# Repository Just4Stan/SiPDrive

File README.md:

# SiPDrive (Work In Progress, Status: Ordering first hardware)

**Compact Field-Oriented Control (FOC) firmware and hardware for QDD actuators**

SiPDrive is an open-source motor controller built around the STSPIN32G4 System-in-Package, MT6701 magnetic encoder, and CAN-FD communication. It targets compact quasi-direct-drive (QDD) actuator applications with torque, position, and speed control.

| | Status |
|---|---|
| **Build** | Compiles (macOS ARM GCC 15.2.0) |
| **Hardware** | PCB designed, ordering assembled from JLCPCB |
| **Firmware** | ~3,100 LOC, 11 KB Flash (8.4%), 13 KB RAM (59%) |
| **License** | CC BY-NC 4.0 |

### Key Features

- 40 kHz FOC current loop with hardware CORDIC acceleration
- CAN-FD command/telemetry (1 Mbps nominal, 5 Mbps data)
- Current and position control modes
- 14-bit magnetic encoder (MT6701 SSI/ABZ selectable via solder jumper)
- On-device encoder calibration with 128-entry compensation table
- Persistent configuration in flash (CRC32 protected)
- Thermal derating and fault protection (board + stator NTC)
- Space Vector PWM (SVPWM) with configurable duty limits

---

## Quick Start

### Prerequisites

```bash
# macOS
brew install arm-none-eabi-gcc cmake
```

### Fetch Dependencies

```bash
cd external
git clone --depth 1 --branch 5.9.0 https://github.com/ARM-software/CMSIS_5.git CMSIS
git clone --depth 1 https://github.com/STMicroelectronics/cmsis_device_g4.git
```

### Build

```bash
cmake -B build \
  -DCMAKE_TOOLCHAIN_FILE=cmake/arm-none-eabi-gcc.cmake \
  -DCMAKE_BUILD_TYPE=Release \
  -DSIPDRIVE_CMSIS_CORE_DIR=external/CMSIS/CMSIS/Core/Include \
  -DSIPDRIVE_STM32G4_DEVICE_DIR=external/cmsis_device_g4

cmake --build build
```

Outputs: `build/SiPDrive.elf`, `.bin`, `.hex`, `.map`

### Flash

```bash
# ST-LINK (recommended)
st-flash write build/SiPDrive.bin 0x08000000

# OpenOCD
openocd -f interface/stlink.cfg -f target/stm32g4x.cfg \
  -c "program build/SiPDrive.elf verify reset exit"
```

---

## Repository Layout

```
SiPDrive/
├── src/                    Firmware source (~3,100 LOC)
├── hw/SiPDrive/            KiCad schematic, PCB, datasheets
├── cmake/                  Toolchain configuration
├── link/                   Linker script (STM32G431)
└── external/               CMSIS dependencies (not vendored)
```

---

<details>
<summary><h2>Hardware Architecture</h2></summary>

### Core Components

**STSPIN32G4 (U1)** - System-in-Package containing:
- STM32G431CBU6 (Cortex-M4F @ 170 MHz)
- Integrated 3-phase gate driver
- Buck converter for MCU power
- 3x operational amplifiers for current sensing
- Memory: 128 KB Flash, 22 KB SRAM + 10 KB CCM RAM

**MT6701 (U2)** - 14-bit magnetic angle sensor
- SSI (default, MODE=HIGH) or ABZ mode (JP1 solder jumper to GND)
- PB7=DO/A, PB6=CLK/B, PB4=CSN/Z

**TCAN1057A (U3)** - CAN-FD transceiver (up to 5 Mbps)

### Pin Assignments

| Peripheral | Function | Pins |
|---|---|---|
| TIM1 | 3-phase PWM (internal to STSPIN32G4 gate driver) | GHS/GLS via 20R gate resistors |
| TIM4 | QEI encoder (ABZ mode) or SPI (SSI mode) | PB7=DO/A, PB6=CLK/B, PB4=CSN/Z |
| OPAMP1 | Phase U current (Ia) | PA1(+), PA3(-), PA2(out) |
| OPAMP2 | Phase W current (Ic) | PA7(+), PC5(-), PA6(out) |
| OPAMP3 | Phase V current (Ib) | PB0(+), PB2(-), PB1(out) |
| ADC1/2 | Vbus, board NTC, stator NTC | PC0 (IN6), PC1 (IN7), PC2 (IN8) |
| FDCAN1 | CAN-FD | PA11=RX, PA12=TX, PA10=TCAN standby |
| I2C3 | STSPIN32G4 gate driver config | Internal SiP bus (no external pins) |
| CORDIC | Hardware sin/cos | - |

### Current Sensing

3-shunt topology with biased differential OPAMPs (EVL reference design):
- **Shunts**: 3x 2 mR (SME08A1FR002T, 0805 1W) on low-side MOSFET sources
- **OPAMP gain**: 10x (Rf=15k / Rin=1.5k), mid-rail bias via 30k/30k divider on OPAMP+ nodes
- **MOSFETs**: 6x CMSA015N06 with 20R gate resistors

### Hardware Constraints

- **128 KB Flash** total - code size must be minimized
- **SCREF overcurrent**: 0.30V threshold via 100k/10k divider (~150A trip with 2 mR shunts)
- **MT6701 MODE**: R6 10k pullup = SSI default, JP1 jumper to GND for ABZ mode
- **Stator NTC (R14)**: DNP solder pad for external thermistor

### KiCad Project

- Schematic: `hw/SiPDrive/SiPDrive.kicad_sch`
- PCB: `hw/SiPDrive/SiPDrive.kicad_pcb`
- Netlist: `hw/SiPDrive/SiPDrive.net`
- Custom libraries: `hw/SiPDrive/kicad/libs/`
- Production outputs: `hw/SiPDrive/production/`

</details>

<details>
<summary><h2>Firmware Architecture</h2></summary>

### Source Layout

| File | Purpose |
|---|---|
| `main.cc` | Main loop, CAN protocol, control loop ISR |
| `config.h` | Compile-time constants |
| `foc_core.{h,cc}` | Clarke/Park transforms, PI current control |
| `position_control.{h,cc}` | Position/velocity PID |
| `calibration.{h,cc}` | Encoder calibration state machine |
| `hal_tim1_pwm.{h,cc}` | TIM1 PWM + 40 kHz ISR |
| `hal_adc_opamp.{h,cc}` | ADC + OPAMP (injected + regular) |
| `hal_qei.{h,cc}` | Quadrature encoder (TIM3/4) |
| `hal_fdcan.{h,cc}` | CAN-FD driver |
| `hal_i2c3_stspin.{h,cc}` | Gate driver I2C config |
| `hal_flash.{h,cc}` | Flash read/write |
| `hal_gpio.{h,cc}` | GPIO utilities |
| `thermal.{h,cc}` | NTC monitoring + derating |
| `persistent_config.{h,cc}` | Flash config (CRC protected) |
| `runtime_support.cc` | Math/string fallbacks (no newlib) |

### Startup Sequence

1. Enable DWT cycle counter
2. Load persistent config from flash (or defaults)
3. Init STSPIN32G4 gate driver via I2C3
4. Init TIM1 PWM (40 kHz) + register ISR
5. Init ADC + OPAMP, calibrate current offsets (1024 samples)
6. Init QEI encoder interface
7. Init FDCAN
8. Apply config (PID gains, thermal limits, calibration)
9. Enable TIM1 and power stage
10. Enter main loop

### Main Loop (~1 kHz)

- Service regular ADC (Vbus, NTC temperatures)
- Update thermal protection
- Handle CAN-FD RX (command frames)
- Run calibration state machine (if active)
- Send telemetry (10 Hz heartbeat)
- Sleep via `__WFI()`

### Control Loop ISR (40 kHz)

1. Check fault conditions (hardware, thermal)
2. Sample encoder position/velocity
3. Read injected ADC (Ia, Ib)
4. Compute Id/Iq command (current mode: direct, position mode: PID cascade)
5. Apply thermal derating
6. FOC pipeline: Clarke -> Park (CORDIC) -> PI controllers -> inverse Park -> SVPWM
7. Update TIM1 duty cycles
8. Queue telemetry if heartbeat due

### HAL Abstraction

All hardware access is through `hal_*` modules. When modifying HAL code, ensure ISR timing is preserved. Use `SIPDRIVE_DEBUG_TIMING=ON` to profile via GPIO.

</details>

<details>
<summary><h2>FOC Algorithm</h2></summary>

Implementation in `foc_core.cc`:

**Clarke Transform** (3-shunt, using Ia and Ib; Ic available for validation):
```
i_alpha = ia
i_beta  = (ia + 2*ib) / sqrt(3)
```

**Park Transform** (using CORDIC hardware, Q1.31 format):
```
id =  cos(theta)*i_alpha + sin(theta)*i_beta
iq = -sin(theta)*i_alpha + cos(theta)*i_beta
```

**PI Current Controllers** (independent Id/Iq):
- Default Kp = 0.30, Ki = 200.0
- Anti-windup: integrator clamped to +/-Vbus/2

**SVPWM**: Common-mode voltage centering, duty range 2%-98%

</details>

<details>
<summary><h2>Control Modes</h2></summary>

### Current Mode (`Mode::kCurrent`)
- Direct Id/Iq control
- 4-byte CAN frame: `[Id_mA, Iq_mA]` (int16 LE)

### Position Mode (`Mode::kPosition`)
- Cascaded PID: position -> velocity -> Iq
- Gains scaled by kp_scale, kd_scale (0.0-1.0)
- 16-byte CAN-FD frame (see protocol section)

</details>

<details>
<summary><h2>CAN-FD Protocol</h2></summary>

### Command Frame (default ID: 0x101)

**4-byte legacy** (current control):

| Byte | Field | Type |
|---|---|---|
| 0-1 | Id | int16 mA, LE |
| 2-3 | Iq | int16 mA, LE |
| 4 | Flags | bit0=clear fault, bit1=start cal |

**16-byte extended** (position/current):

| Byte | Field | Type |
|---|---|---|
| 0-3 | Position | float32 rad, LE (NaN = no position loop) |
| 4-7 | Velocity | float32 rad/s, LE |
| 8-9 | Max torque | int16 mA, LE |
| 10-11 | kp_scale | uint16, 0-32767 maps to 0.0-1.0 |
| 12-13 | kd_scale | uint16, 0-32767 maps to 0.0-1.0 |
| 14 | Flags | same as legacy |
| 15 | Mode | 0=current, 1=position |

### Telemetry Frame (default ID: 0x181, 24 bytes, 10 Hz)

| Byte | Field | Type |
|---|---|---|
| 0-3 | Position | float32 rad, LE |
| 4-7 | Velocity | float32 rad/s, LE |
| 8-9 | Iq measured | int16 mA, LE |
| 10-11 | Id measured | int16 mA, LE |
| 12-13 | Vbus | uint16 mV, LE |
| 14-15 | Board temp | int16, 0.01 C, LE |
| 16-17 | Stator temp | int16, 0.01 C, LE |
| 18 | Fault flags | bit0=gate, bit1=CAN, bit2=thermal |
| 19 | Mode | current mode enum |
| 20-23 | Reserved | - |

</details>

<details>
<summary><h2>Configuration</h2></summary>

### Persistent Configuration

Stored in flash (last page), CRC32 protected, magic `0x4D4D4347`.

Fields: motor pole pairs, current limit, PID gains (position Kp/Ki/Kd, velocity Kp/Ki), velocity limit, thermal thresholds, CAN IDs, encoder calibration (offset + 128-entry table).

### Compile-Time Configuration (`config.h`)

| Parameter | Default | Description |
|---|---|---|
| `SIPDRIVE_SYS_CLOCK_HZ` | 170 MHz | PLL or 16 MHz HSI |
| `SIPDRIVE_CONTROL_LOOP_HZ` | 40000 | Control loop rate |
| `SIPDRIVE_PWM_FREQUENCY_HZ` | 40000 | PWM frequency |
| `SIPDRIVE_TIM1_DEADTIME_NS` | 250 | Gate driver deadtime |
| `SIPDRIVE_ENCODER_CPR` | 16384 | MT6701 14-bit |

### CMake Options

| Option | Default | Description |
|---|---|---|
| `SIPDRIVE_USE_PLL170` | ON | 170 MHz PLL clock |
| `SIPDRIVE_USE_BKIN` | OFF | TIM1 break input (PE15) |
| `SIPDRIVE_DEBUG_TIMING` | OFF | GPIO ISR profiling |

### Adding a New Parameter

1. Add CMake cache variable in `CMakeLists.txt`
2. Add `target_compile_definitions` pass-through
3. Add `#ifndef` fallback + `constexpr` in `config.h`

</details>

<details>
<summary><h2>Encoder Calibration</h2></summary>

Implemented in `calibration.cc`. Compensates encoder non-linearity and determines electrical angle offset.

1. **Forward sweep**: Drive motor with fixed d-axis voltage, sweep electrical angle 0 to 2pi, record encoder error
2. **Reverse sweep**: Repeat in opposite direction to average out cogging torque
3. **Compute table**: 128-entry lookup (encoder angle to correction)
4. **Save to flash**: Electrical offset + compensation table persisted

Trigger calibration via CAN command flag bit 1. Motor must be free to rotate.

</details>

<details>
<summary><h2>Thermal Protection</h2></summary>

Two-level protection per sensor (board NTC, stator NTC):

1. **Warning**: Linear current derating from (fault_temp - margin) to fault_temp
2. **Fault**: Power stage disabled above fault threshold

Defaults: board 120 C fault / 25 C margin, stator 150 C fault / 25 C margin.

NTC thermistors read via ADC at ~1 kHz with piecewise lookup-table interpolation.

</details>

<details>
<summary><h2>Build System Details</h2></summary>

### Toolchain

- ARM GCC 15.2.0 (`arm-none-eabi-gcc`)
- CMake >= 3.20
- Cortex-M4F hard-float configuration

### Dependencies

| Dependency | Location | Source |
|---|---|---|
| CMSIS Core 5.9.0 | `external/CMSIS/` | github.com/ARM-software/CMSIS_5 |
| STM32G4 Device | `external/cmsis_device_g4/` | github.com/STMicroelectronics/cmsis_device_g4 |

### Custom Runtime (`runtime_support.cc`)

Provides `sinf`, `cosf`, `sqrtf`, `fmodf`, `atan2f`, `fabsf`, `memset`, `memcpy`, `memmove`, `memcmp`. Needed because Homebrew ARM toolchain lacks newlib. Uses Taylor series approximations - accuracy ~0.001 for trig functions.

### Memory Layout (linker script: `link/stm32g431vb.ld`)

| Region | Address | Size |
|---|---|---|
| FLASH | 0x08000000 | 128 KB |
| RAM | 0x20000000 | 22 KB |
| CCMRAM | 0x10000000 | 10 KB |

### Current Memory Usage

```
FLASH    11,056 B / 128 KB   8.44%
RAM      13,344 B /  22 KB  59.23%
CCM RAM   8,192 B /  10 KB  80.00%
```

Stack is 4 KB, not yet profiled on hardware.

### Verification

```bash
arm-none-eabi-size -A build/SiPDrive.elf
arm-none-eabi-nm -C -S --size-sort build/SiPDrive.elf
```

### Known Build Issues

1. **FDCAN RXESC/TXESC** registers missing from STM32G431 CMSIS headers (lines commented out in `hal_fdcan.cc`)
2. **Math approximations** - Taylor series trig may need improvement for production
3. **No unit tests** - FOC math validated by inspection only

### Datasheets

Component datasheets are in `hw/SiPDrive/datasheets/`. The STM32G4 reference manual (RM0440, ~37 MB) is gitignored to keep clone size down. Download it directly from [ST](https://www.st.com/resource/en/reference_manual/rm0440-stm32g4-series-advanced-armbased-32bit-mcus-stmicroelectronics.pdf) and place at:
```
hw/SiPDrive/datasheets/rm0440-stm32g4-series-advanced-armbased-32bit-mcus-stmicroelectronics.pdf
```

</details>

<details>
<summary><h2>Bring-Up Workflow</h2></summary>

### Pre-Flight Checklist

- [ ] Motor pole pairs match `config.h` (`kMotorPolePairs = 7`)
- [ ] Encoder CPR correct (`kEncoderCountsPerRev = 16384`)
- [ ] Shunt value correct (`kShuntOhm = 0.002`)
- [ ] OPAMP gain matches hardware (`kOpampGain = 10.0`)
- [ ] Current limits set appropriately
- [ ] Bus voltage safe (`kBusVoltageV = 24.0f`)
- [ ] Thermal limits reviewed

### Step-by-Step

1. **Bench setup**: Current-limited supply, motor free, ST-LINK connected, CAN-FD adapter with 120 ohm termination

2. **Flash**: `st-flash write build/SiPDrive.bin 0x08000000`

3. **CAN-FD host setup**:
   ```bash
   sudo ip link set can0 down
   sudo ip link set can0 type can bitrate 1000000 dbitrate 5000000 fd on
   sudo ip link set can0 up
   ```

4. **Verify telemetry**: `candump can0,181:7FF`

5. **Low-current test** (Id=0, Iq=1000 mA):
   ```bash
   cansend can0 101##10000E803
   ```

6. **Position mode**: Only after current control is validated. Start with small torque limits and low gains.

7. **Calibration**: Set command flag bit 1 in CAN frame.

8. **Validate**: PWM outputs, current polarity, encoder direction, thermal/fault behavior.

### Safety Warnings

- Code is **untested** - expect bugs
- Current sensing polarity is **unknown** until verified
- Electrical angle offset requires **calibration**
- No hardware current limit - **software only**
- Stack usage is **unprofiled**

</details>

<details>
<summary><h2>Schematic Audit (2026-02-14)</h2></summary>

Validated against STSPIN32G4, EVLSPIN32G4-ACT, MT6701, and TCAN1057A datasheets.

**Verdict**: Schematic is ready for PCB layout.

### Current Sensing (validated)

3-shunt biased differential topology matching EVLSPIN32G4-ACT reference:
- 30k/30k bias dividers on OPAMP+ nodes (PA1, PA7, PB0) - provides 1.65V mid-rail DC bias
- 1.5k input resistors from shunt nodes to OPAMP+ inputs
- 15k/1.5k feedback gives 10x differential gain
- 2 mR shunts (SME08A1FR002T, 0805 1W) — full-scale ±82.5A, ~40 mA/LSB resolution

### SCREF Divider (valid)

R15=100k / R37=10k / C30=33n gives VSCREF = 0.300 V. Within STSPIN32G4 valid range (0.2 V to 2.55 V). Estimated trip current ~120 A for 2.5 mohm RDS(on).

### 6S Battery Divider (valid)

R10=100k / R9=10k gives gain 11. At 25.2 V max: Vadc = 2.29 V (within 3.3 V range).

### Inter-IC Validation

| Connection | Status |
|---|---|
| U1 PB7 <-> U2 A (encoder) | Pass |
| U1 PB6 <-> U2 B (encoder) | Pass |
| U1 PB4 <-> U2 Z (encoder) | Pass |
| U2 MODE (strap R6 + JP1) | Pass |
| U1 PA12 -> U3 TXD (CAN) | Pass |
| U1 PA11 <- U3 RXD (CAN) | Pass |
| U1 PA10 -> U3 S (CAN mode) | Pass |

### Remaining Items

1. Clean KiCad ERC warnings (PWR_FLAG hygiene, unused pin markers)
2. Consider adding dedicated VREF+ filtering (ferrite + cap) for improved ADC accuracy in production

</details>

<details>
<summary><h2>Comparison to moteus</h2></summary>

SiPDrive is inspired by [mjbots moteus](https://github.com/mjbots/moteus) but optimized for compactness:

| Feature | moteus | SiPDrive |
|---|---|---|
| MCU | STM32G474 (512K Flash, 128K RAM) | STM32G431 (128K Flash, 32K RAM) |
| Gate Driver | DRV8323 (external) | STSPIN32G4 (integrated SiP) |
| Current Sensing | 3-phase | 3-phase (3x 2 mR shunts, 10x OPAMP) |
| Build System | Bazel + mbed-os | CMake + bare-metal |
| Control Rate | 30 kHz | 40 kHz |
| Communication | CAN-FD + RS485 | CAN-FD only |
| Encoder | AS5047P (SPI) | MT6701 (SSI/ABZ, jumper selectable) |
| Form Factor | Standalone PCB | Compact (motor-mounted) |
| Maturity | Production | Alpha (untested) |
| Binary Size | ~100 KB+ | 11 KB |

### Functional Gaps vs moteus `fw`

SiPDrive is intentionally minimal (~3.7k LOC vs ~21.7k LOC). Key differences:

**Control**: Only current + position modes. Missing: voltage modes, trajectory shaping, torque model, feedforward.

**Protocol**: Fixed CAN frames. Missing: register-based protocol, multiplex server, dynamic config.

**Sensing**: MT6701 SSI/ABZ via jumper. Missing: multi-source position pipeline, AUX port support.

**Safety**: Basic fault flags + thermal. Missing: structured fault codes, timing violation detection, command timeout.

**Testing**: No unit tests or simulation. Missing: host-side protocol tests, regression suite, bootloader.

</details>

<details>
<summary><h2>Roadmap</h2></summary>

### P0: Bring-Up and Controllability
- CAN-FD payload sizing hardening (RXESC/TXESC)
- Host control tooling (Python `python-can` script)
- Safety minimums: UV/OV faults, watchdog (IWDG), fault latching
- Lock MT6701 MODE strategy, validate encoder paths
- Commissioning flow: flash -> telemetry -> low-current spin -> calibration

### P1: Control Quality
- Motor characterization (R, L, electrical direction)
- Loop-rate separation (velocity/position at lower rate)
- Telemetry expansion (electrical angle, duty, loop errors)

### P2: Production-Ready
- Control deadline monitoring
- DMA for regular ADC
- Field weakening, MTPA, optional sensorless estimator

### Future
- CAN bootloader for field updates
- Register-based protocol (moteus compatibility)
- Advanced calibration (multi-turn, temp compensation)
- Host-side unit tests for FOC math and protocol
- Stack profiling and memory optimization

### Known Limitations

- Firmware currently uses only 2 of 3 OPAMP channels (3rd available for validation)
- No hardware overcurrent protection
- PWM frequency not runtime-configurable
- No FOC decoupling (back-EMF, cross-coupling feedforward)
- Taylor series math may be insufficient for high-performance FOC

</details>

<details>
<summary><h2>Debugging and Troubleshooting</h2></summary>

### No Current Sensing
- Check OPAMP config in `hal_adc_opamp.cc`
- Verify ADC injected channels match OPAMP outputs
- Scope OPAMP outputs (should be 0-3.3 V)

### Motor Not Spinning
- Scope TIM1 PWM outputs
- Verify gate driver enabled (`hal_i2c3_stspin.cc`)
- Check fault flags in telemetry
- Verify encoder reads valid position

### Encoder Calibration Fails
- Motor must be free to rotate
- Check ABZ signal connections
- Verify QEI config (`hal_qei.cc`)

### CAN Issues
- Check transceiver wiring and bus termination (120 ohm)
- Verify bitrate: nominal 1 Mbps, data 5 Mbps, FD+BRS
- Debug with `candump can0`

### Debug Tools
- `SIPDRIVE_DEBUG_TIMING=ON`: GPIO toggle on PC14 for ISR profiling
- SWD via ST-LINK + GDB: `arm-none-eabi-gdb build/SiPDrive.elf`
- CAN sniffing: `candump can0`

</details>

<details>
<summary><h2>Code Style</h2></summary>

- **C++17** (configured in CMakeLists.txt)
- Classes: `PascalCase`
- Functions: `PascalCase`
- Variables: `snake_case`
- Constants: `kPascalCase`
- Members: `snake_case_` (trailing underscore)
- Namespaces: `sipdrive::module`
- Headers: `#pragma once`
- ISR code should be inlined; use `__attribute__((hot))` for critical paths

</details>

<details>
<summary><h2>Common Tasks</h2></summary>

### Modifying FOC Gains

Compile-time in `config.h`:
```cpp
constexpr float kIdKp = 0.30f;
constexpr float kIdKi = 200.0f;
constexpr float kIqKp = 0.30f;
constexpr float kIqKi = 200.0f;
```

### Adding a New CAN Command

1. Add handler in `main.cc` `HandleCommandFrame()`
2. Parse frame data with byte helpers (`ReadFloatLe`, etc.)
3. Update global state
4. Document protocol

### Adding a New Fault

1. Add fault flag bit in telemetry definition
2. Implement detection in main loop or ISR
3. Set fault variable (`volatile bool`)
4. In `ControlLoopIsr()`, check and disable power stage
5. Add clear mechanism via CAN command flag

</details>

---

## References

- [STSPIN32G4 Datasheet](hw/SiPDrive/datasheets/stspin32g4.pdf)
- [MT6701 Datasheet](hw/SiPDrive/datasheets/MT6701.pdf)
- [TCAN1057A-Q1 Datasheet](hw/SiPDrive/datasheets/tcan1057a-q1.pdf)
- [STM32G431 Datasheet](hw/SiPDrive/datasheets/stm32g431c6.pdf)
- STM32G4 Reference Manual (RM0440) - [download from ST](https://www.st.com/resource/en/reference_manual/rm0440-stm32g4-series-advanced-armbased-32bit-mcus-stmicroelectronics.pdf) (gitignored, 37 MB)
- FOC Theory: "Vector Control of AC Machines" (Peter Vas)
- SVPWM: ST Application Note AN4013

## License

This project is licensed under [CC BY-NC 4.0](https://creativecommons.org/licenses/by-nc/4.0/) - free for all non-commercial use. See [LICENSE](LICENSE) for details.

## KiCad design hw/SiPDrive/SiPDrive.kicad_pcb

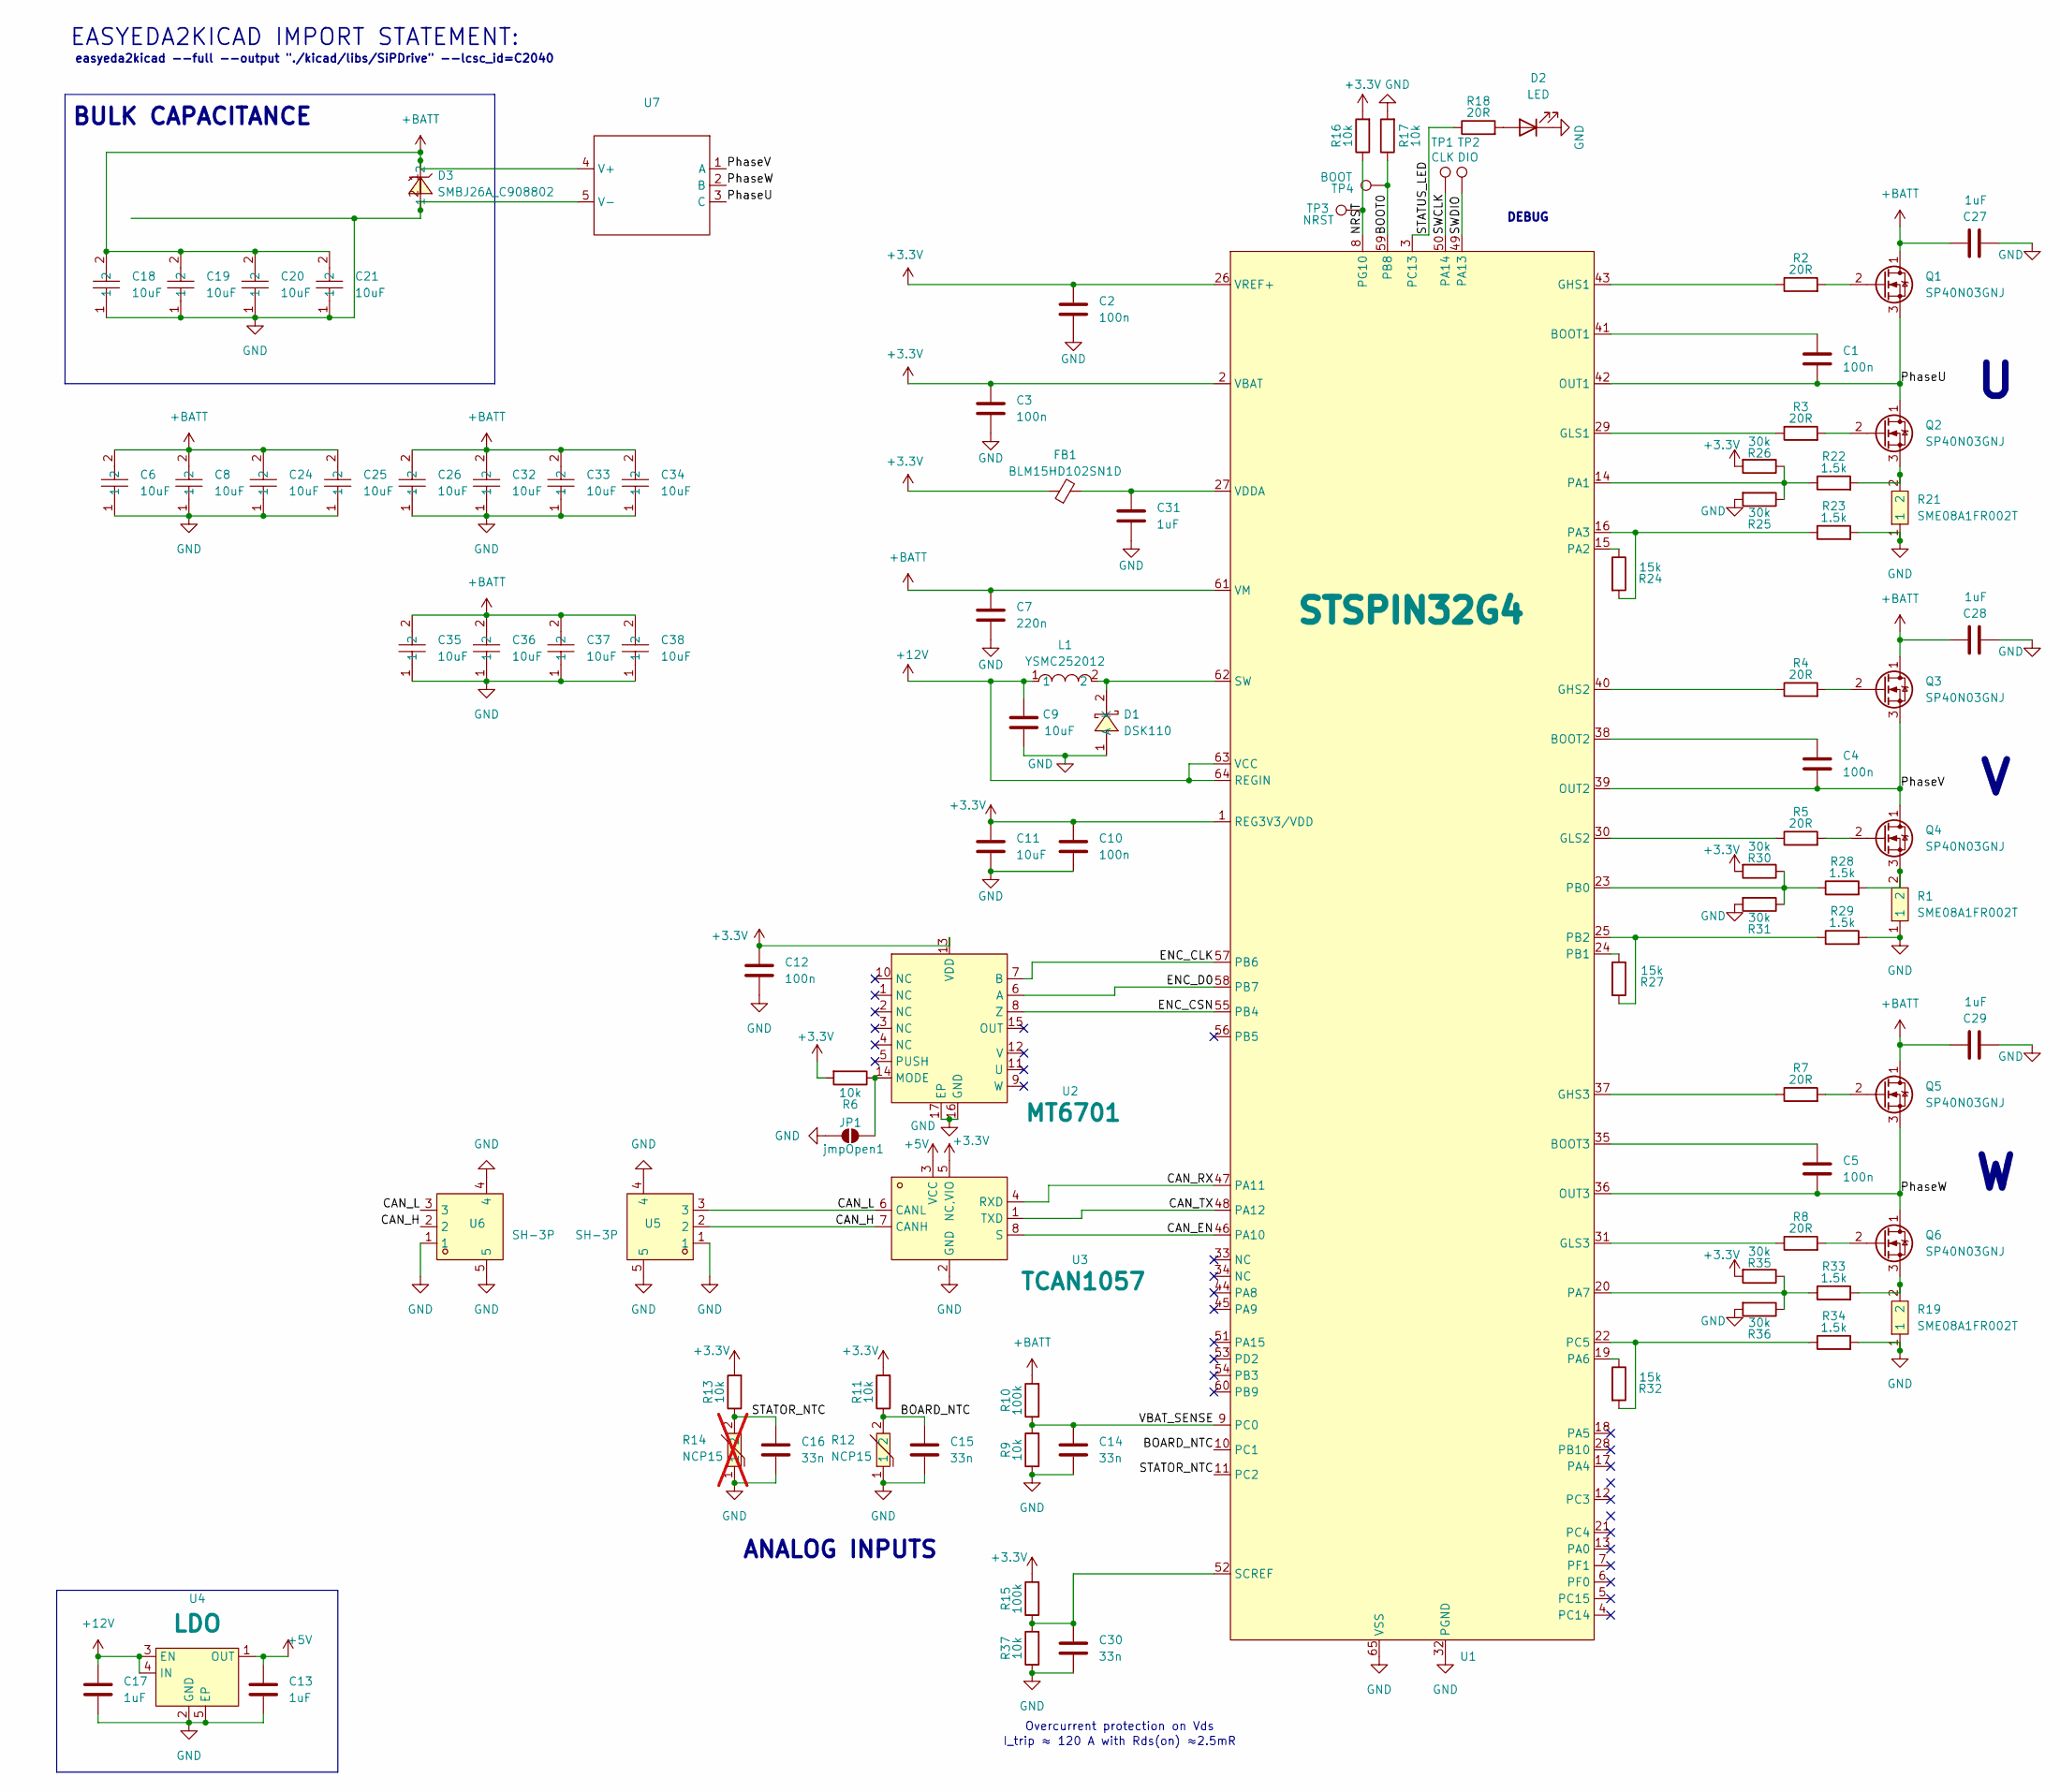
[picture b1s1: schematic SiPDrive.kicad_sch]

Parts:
C1, C2, C3, C4, C5, C10, C12: 100n; C_0201_0603Metric; LCSC C181043
C6, C8, C18, C19, C20, C21, C24, C25, C26, C32, C33, C34, C35, C36, C37, C38: 10uF; C_1206_3216Metric; LCSC C5119295
C7: 220n; C_0402_1005Metric; LCSC C49333232
C9: 10uF; C_0603_1608Metric; LCSC C96446
C11: 10uF; C_0402_1005Metric; LCSC C15525
C13, C17: 1uF; C_0402_1005Metric; LCSC C52923
C14, C15, C16, C30: 33n; C_0201_0603Metric; LCSC C161475
C27, C28, C29: 1uF; C_0402_1005Metric; LCSC C1518208
C31: 1uF; C_0402_1005Metric; LCSC C14445
D1: DSK110; SOD-123_L2.8-W1.8-LS3.7-FD; LCSC C908227
D2: LED; LED_0402_1005Metric; LCSC C20608784
D3: SMBJ26A_C908802; SMB_L4.5-W3.7-LS5.4-RD; LCSC C908802
FB1: BLM15HD102SN1D; C_0402_1005Metric; LCSC C21516
JP1: jmpOpen1; SolderJumper-2_P1.3mm_Open_RoundedPad1.0x1.5mm
L1: YSMC252012; L1008; LCSC C41405922
Q1, Q2, Q3, Q4, Q5, Q6: SP40N03GNJ; POWERPAK-1212-8_L3.0-W3.0-P0.65-LS3.3-BL; LCSC C22466709
R1, R19, R21: SME08A1FR002T; R0508; LCSC C2692045
R2, R3, R4, R5, R7, R8, R18: 20R; R_0201_0603Metric; LCSC C473548
R6, R9, R11, R13, R16, R17, R37: 10k; R_0201_0603Metric; LCSC C473048
R10, R15: 100k; R_0201_0603Metric; LCSC C270364
R12: NCP15; R0402; LCSC C77131
R14: NCP15; C_0805_2012Metric; LCSC C77131; not fitted
R22, R23, R28, R29, R33, R34: 1.5k; R_0201_0603Metric; LCSC C270361
R24, R27, R32: 15k; R_0201_0603Metric; LCSC C473452
R25, R26, R30, R31, R35, R36: 30k; R_0201_0603Metric; LCSC C246933
TP1: CLK; TestPoint_Pad_D1.0mm
TP2: DIO; TestPoint_Pad_D1.0mm
TP3: NRST; TestPoint_Pad_D1.0mm
TP4: BOOT; TestPoint_Pad_D1.0mm
U1: STSPIN32G4; VFQFPN-64_L9.0-W9.0-P0.50-TL-EP4.0; LCSC C7434864
U2: MT6701; QFN-16_L3.0-W3.0-P0.50-TL-EP1.7; LCSC C2913974
U3: TCAN1057; TSOT-23-8_L2.9-W1.6-P0.65-LS2.8-BR; LCSC C3236208
U4: LDO; UDFN-4_L1.0-W1.0-P0.65-BL-EP; LCSC C39673733
U5, U6: SH-3P; CONN-SMD_SM03B-SRSS-TB-LF-SN-P; LCSC C160403
U7: SiPDrive_EDGE

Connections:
+3.3V: C2.1, C3.1, C10.1, C11.1, C12.1, FB1.1, R6.2, R11.2, R13.2, R15.2, R16.2, R26.2, R30.2, R35.2, U1.1 (REG3V3/VDD), U1.2 (VBAT), U1.26 (VREF+), U2.13 (VDD), U3.5 (NC,VIO)
+5V: C13.1, U3.3 (VCC), U4.1 (OUT)
+12V: C9.1, C17.1, L1.1, U1.63 (VCC), U1.64 (REGIN), U4.3 (EN), U4.4 (IN)
+BATT: C6.2, C7.1, C8.2, C18.2, C19.2, C20.2, C21.2, C24.2, C25.2, C26.2, C27.1, C28.1, C29.1, C32.2, C33.2, C34.2, C35.2, C36.2, C37.2, C38.2, D3.1, Q1.1 (D), Q3.1 (D), Q5.1 (D), R10.2, U1.61 (VM), U7.4 (V+)
/BOARD_NTC: C15.1, R11.1, R12.2, U1.10 (PC1)
/BOOT0: R17.1, TP4.1, U1.59 (PB8)
/CAN_EN: U1.46 (PA10), U3.8 (S)
/CAN_H: U3.7 (CANH), U5.2, U6.2
/CAN_L: U3.6 (CANL), U5.3, U6.3
/CAN_RX: U1.47 (PA11), U3.4 (RXD)
/CAN_TX: U1.48 (PA12), U3.1 (TXD)
/ENC_CLK: U1.57 (PB6), U2.7 (B)
/ENC_CSN: U1.55 (PB4), U2.8 (Z)
/ENC_D0: U1.58 (PB7), U2.6 (A)
/NRST: R16.1, TP3.1, U1.8 (PG10)
/PhaseU: C1.2, Q1.3 (S), Q2.1 (D), U1.42 (OUT1), U7.3 (C)
/PhaseV: C4.2, Q3.3 (S), Q4.1 (D), U1.39 (OUT2), U7.1 (A)
/PhaseW: C5.2, Q5.3 (S), Q6.1 (D), U1.36 (OUT3), U7.2 (B)
/STATOR_NTC: C16.1, R13.1, R14.2, U1.11 (PC2)
/STATUS_LED: R18.1, U1.3 (PC13)
/SWCLK: TP1.1, U1.50 (PA14)
/SWDIO: TP2.1, U1.49 (PA13)
/VBAT_SENSE: C14.1, R9.2, R10.1, U1.9 (PC0)
GND: C2.2, C3.2, C6.1, C7.2, C8.1, C9.2, C10.2, C11.2, C12.2, C13.2, C14.2, C15.2, C16.2, C17.2, C18.1, C19.1, C20.1, C21.1, C24.1, C25.1, C26.1, C27.2, C28.2, C29.2, C30.2, C31.2, C32.1, C33.1, C34.1, C35.1, C36.1, C37.1, C38.1, D1.1 (A), D2.1 (K), D3.2, JP1.1 (A), R1.1, R9.1, R12.1, R14.1, R17.2, R19.1, R21.1, R23.2, R25.2, R29.2, R31.2, R34.2, R36.2, R37.1, U1.32 (PGND), U1.65 (VSS), U2.16 (GND), U2.17 (EP), U3.2 (GND), U4.2 (GND), U4.5 (EP), U5.1, U5.4, U5.5, U6.1, U6.4, U6.5, U7.5 (V-)
unnamed: D1.2 (K), L1.2, U1.62 (SW)
unnamed: D2.2 (A), R18.2
unnamed: JP1.2 (B), R6.1, U2.14 (MODE)
unnamed: Q1.2 (G), R2.2
unnamed: Q2.2 (G), R3.2
unnamed: Q2.3 (S), R21.2, R22.2
unnamed: Q3.2 (G), R4.2
unnamed: Q4.2 (G), R5.2
unnamed: Q4.3 (S), R1.2, R28.2
unnamed: Q5.2 (G), R7.2
unnamed: Q6.2 (G), R8.2
unnamed: Q6.3 (S), R19.2, R33.2
unnamed: C1.1, U1.41 (BOOT1)
unnamed: C4.1, U1.38 (BOOT2)
unnamed: C5.1, U1.35 (BOOT3)
unnamed: R2.1, U1.43 (GHS1)
unnamed: R4.1, U1.40 (GHS2)
unnamed: R7.1, U1.37 (GHS3)
unnamed: R3.1, U1.29 (GLS1)
unnamed: R5.1, U1.30 (GLS2)
unnamed: R8.1, U1.31 (GLS3)
unnamed: R22.1, R25.1, R26.1, U1.14 (PA1)
unnamed: R24.1, U1.15 (PA2)
unnamed: R23.1, R24.2, U1.16 (PA3)
unnamed: R32.1, U1.19 (PA6)
unnamed: R33.1, R35.1, R36.1, U1.20 (PA7)
unnamed: R28.1, R30.1, R31.1, U1.23 (PB0)
unnamed: R27.1, U1.24 (PB1)
unnamed: R27.2, R29.1, U1.25 (PB2)
unnamed: R32.2, R34.1, U1.22 (PC5)
unnamed: C30.1, R15.1, R37.2, U1.52 (SCREF)
unnamed: C31.1, FB1.2, U1.27 (VDDA)

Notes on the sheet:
DEBUG
easyeda2kicad --full --output "./kicad/libs/SiPDrive" --lcsc_id=C2040
I_trip ≈ 120 A with Rds(on) ≈2.5mR
BULK CAPACITANCE
Overcurrent protection on Vds
ANALOG INPUTS
EASYEDA2KICAD IMPORT STATEMENT:

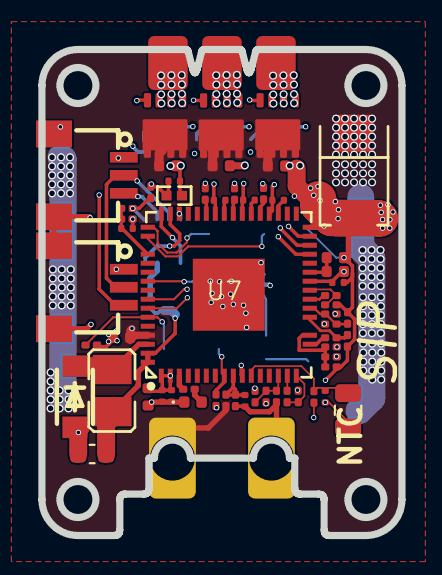
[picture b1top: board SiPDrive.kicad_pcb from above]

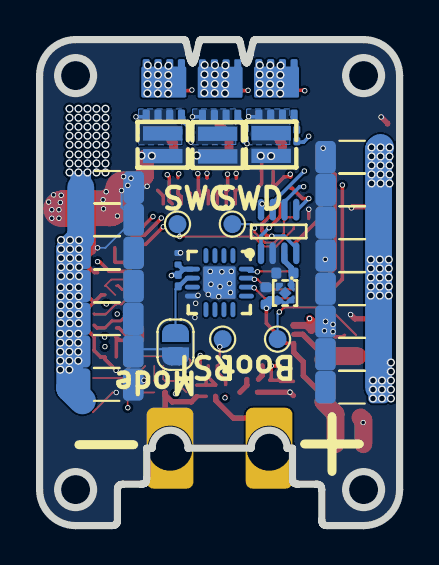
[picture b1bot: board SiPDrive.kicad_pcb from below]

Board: 6 copper layers, 20.0 x 27.0 mm, 94 parts (36 on the bottom side), 56 nets.

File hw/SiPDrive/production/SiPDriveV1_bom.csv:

Designator,Footprint,Quantity,Value,LCSC Part #
"C1, C10, C12, C2, C3, C4, C5",0201,7,100n,C181043
C11,0402,1,10uF,C15525
"C13, C17",0402,2,1uF,C52923
"C14, C15, C16, C30",0201,4,33n,C161475
"C18, C19, C20, C21, C24, C25, C26, C32, C33, C34, C35, C36, C37, C6, C8",1206,15,10uF,C5119295
"C27, C28, C29",0402,3,1uF,C1518208
C31,0402,1,1uF,C14445
C7,0402,1,220n,C49333232
C9,0603,1,10uF,C96446
D1,SOD-123_L2.8-W1.8-LS3.7-FD,1,DSK110,C908227
D2,0402,1,LED,C20608784
D3,SMB_L4.5-W3.7-LS5.4-RD,1,SMBJ26A_C908802,C908802
FB1,0402,1,BLM15HD102SN1D,C21516
L1,L1008,1,YSMC252012,C41405922
"Q1, Q2, Q3, Q4, Q5, Q6",POWERPAK-1212-8_L3.0-W3.0-P0.65-LS3.3-BL,6,SP40N03GNJ,C22466709
"R1, R19, R21",R0508,3,SME08A1FR002T,C2692045
"R10, R15",0201,2,100k,C270364
"R11, R13, R16, R17, R37, R6, R9",0201,7,10k,C473048
R12,R0402,1,NCP15,C77131
R14,0805,1,NCP15,C77131
"R18, R2, R3, R4, R5, R7, R8",0201,7,20R,C473548
"R22, R23, R28, R29, R33, R34",0201,6,1.5k,C270361
"R24, R27, R32",0201,3,15k,C473452
"R25, R26, R30, R31, R35, R36",0201,6,30k,C246933
TP1,TestPoint_Pad_D1.0mm,1,CLK,
TP2,TestPoint_Pad_D1.0mm,1,DIO,
TP3,TestPoint_Pad_D1.0mm,1,NRST,
TP4,TestPoint_Pad_D1.0mm,1,BOOT,
U1,VFQFPN-64_L9.0-W9.0-P0.50-TL-EP4.0,1,STSPIN32G4,C7434864
U2,QFN-16_L3.0-W3.0-P0.50-TL-EP1.7,1,MT6701,C2913974
U3,TSOT-23-8_L2.9-W1.6-P0.65-LS2.8-BR,1,TCAN1057,C3236208
U4,UDFN-4_L1.0-W1.0-P0.65-BL-EP,1,LDO,C39673733
"U5, U6",CONN-SMD_SM03B-SRSS-TB-LF-SN-P,2,SH-3P,C160403
U7,SiPDrive_EDGE,1,~,

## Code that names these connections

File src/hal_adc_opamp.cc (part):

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
void ConfigureAnalogPins() {
  gpio::EnablePort(GPIOC);
  gpio::ConfigureAnalog(GPIOC, 0U);  // VBAT_SENSE
  gpio::ConfigureAnalog(GPIOC, 1U);  // BOARD_NTC
  gpio::ConfigureAnalog(GPIOC, 2U);  // STATOR_NTC
}

void ConfigureInjectedSequence(ADC_TypeDef* adc, uint8_t channel, InjectedTriggerMode mode) {
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
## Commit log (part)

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2026-02-14 Rebrand and initialize SiPDrive repository
2026-02-16 Updated schematic to a 3 shunt topology and made first deboard PCB layout
2026-02-16 Ordered first dev board and components
2026-02-24 Revise project status in README
    Updated project status in README to indicate it's a work in progress and that hardware needs to be ordered.
2026-03-14 other shunts, redo routing
2026-03-15 started routing
2026-03-16 Final routing, code fixes, production files and BOM
